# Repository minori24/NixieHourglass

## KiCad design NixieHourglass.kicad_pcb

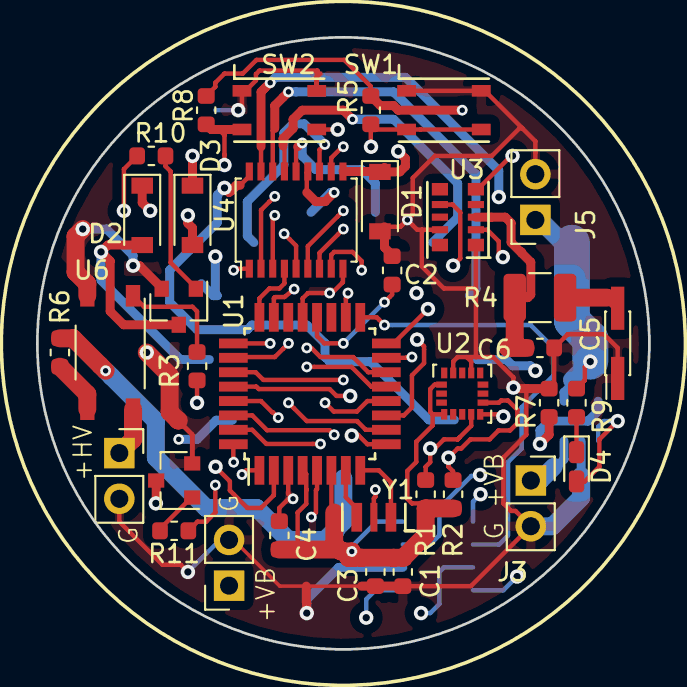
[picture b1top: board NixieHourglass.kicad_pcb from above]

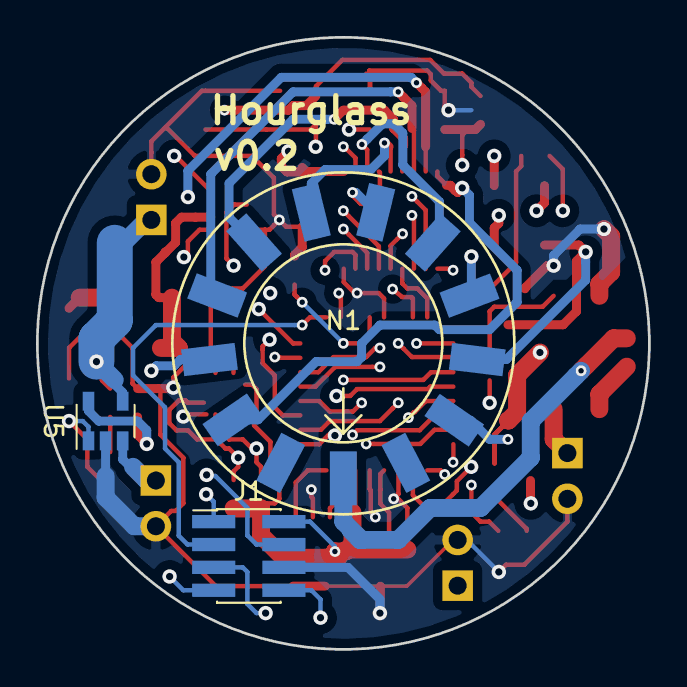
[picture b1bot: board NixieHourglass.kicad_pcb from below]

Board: 4 copper layers, 34.0 x 34.0 mm, 38 parts (3 on the bottom side), 49 nets.

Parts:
C1, C3: 1uF; C_0603_1608Metric
C2, C6: 100nF; C_0603_1608Metric
C4: 4.7uF; C_0603_1608Metric
C5: SE-5R5-D105VYV; PinHeader_2x01_P1.27mm_Vertical_SMD
D1: Zener_47V; D_SOD-123
D2, D3: GS1010FL; D_SOD-123
D4: LED; LED_0603_1608Metric_Castellated
J1: Conn_02x04_Odd_Even; PinHeader_2x04_P1.27mm_Vertical_SMD
J2: VBAT_OUT; PinSocket_1x02_P2.54mm_Vertical
J3: VBAT_IN; PinSocket_1x02_P2.54mm_Vertical
J4: HV_IN; PinSocket_1x02_P2.54mm_Vertical
J5: CHG_IN; PinSocket_1x02_P2.54mm_Vertical
N1: IN-14; IN-14_SMD
Q2, Q3: MMBTA42; SOT-23
R1, R2, R5, R8, R10, R11: 10k; R_0603_1608Metric
R3: 220; R_0603_1608Metric
R4: 1210_ROHM_MCR25JZHJ101; R_1210_3225Metric
R6: 22k; R_0603_1608Metric
R7, R9: R; R_0603_1608Metric
SW1, SW2: SKRPACE010; SW_Tactile_SKRPACE010
U1: ATmega328P-AU; TQFP-32_7x7mm_P0.8mm
U2: LIS3DHTR; LGA-16_3x3mm_P0.5mm_LayoutBorder3x5y
U3: RX8900CE
U4: TD62083AFNG; SSOP-18_4.4x6.5mm_P0.65mm
U5: MCP73832T-2ACI_OT; SOT-23-5
U6: TLP127; MFSOP6-4_4.4x3.6mm_P1.27mm
Y1: CSTCE16M0V53-R0; Xtal_Murata_CSTCE16M0V53-R0

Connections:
+5V: J5.1, R9.1, U5.4
+BATT: C1.1, C3.1, C4.1, J1.2, J2.1, J3.1, R1.1, R2.1, R5.1, R8.1, U1.4, U1.6, U1.18, U2.1, U2.14, U3.2, U5.3
+HV: J4.1, U6.6
/MISO: J1.1, U1.16
/MOSI: J1.4, U1.15
/NIX_0: R11.2, U1.12
/NIX_1: U1.13, U4.1
/NIX_2: U1.14, U4.2
/NIX_3: U1.23, U4.3
/NIX_4: U1.24, U4.4
/NIX_5: U1.25, U4.5
/NIX_6: U1.26, U4.6
/NIX_7: U1.32, U4.7
/NIX_8: U1.1, U4.8
/NIX_9: R10.2, U1.2
/NIX_ANODE: R3.2, U1.10
/RESET: J1.5, U1.29
/RXD: J1.7, U1.30
/SCK: J1.3, U1.17
/TXD: J1.8, U1.31
GND: C1.2, C2.2, C3.2, C4.2, C5.1, C6.2, D1.2, J1.6, J2.2, J3.2, J4.2, J5.2, Q2.2, Q3.2, R7.2, SW1.1, SW1.2, SW2.1, SW2.2, U1.3, U1.5, U1.21, U2.5, U2.10, U2.12, U3.1, U3.9, U4.9, U5.2, U6.3, Y1.2
unnamed: C2.1, U1.20
unnamed: C5.2, R4.1
unnamed: C6.1, R4.2, U3.3
unnamed: D1.1, D2.1, D3.1, U4.10
unnamed: D2.2, N1.9, Q2.3
unnamed: D3.2, N1.0, Q3.3
unnamed: D4.1, R9.2
unnamed: D4.2, U5.1
unnamed: N1.1, U4.18
unnamed: N1.2, U4.17
unnamed: N1.3, U4.16
unnamed: N1.4, U4.15
unnamed: N1.5, U4.14
unnamed: N1.6, U4.13
unnamed: N1.7, U4.12
unnamed: N1.8, U4.11
unnamed: N1.A, R6.2
unnamed: Q2.1, R10.1
unnamed: Q3.1, R11.1
unnamed: R3.1, U6.1
unnamed: R6.1, U6.4
unnamed: R7.1, U5.5
unnamed: U1.7, Y1.3
unnamed: U1.8, Y1.1
SCL: R1.2, U1.28, U2.4, U3.5
SDA: R2.2, U1.27, U2.6, U3.7
SW_0: R5.2, SW1.3, SW1.4, U1.9
SW_1: R8.2, SW2.3, SW2.4, U1.11

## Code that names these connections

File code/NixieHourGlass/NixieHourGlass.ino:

#define PIN_NIX_0 9
#define PIN_NIX_1 8
#define PIN_NIX_2 4
#define PIN_NIX_4 2
#define PIN_NIX_3 3
#define PIN_NIX_5 A3
#define PIN_NIX_6 A2
#define PIN_NIX_7 A1
#define PIN_NIX_8 A0
#define PIN_NIX_9 10
#define PIN_SW_0 5
#define PIN_SW_1 7
#define PIN_NIX_ANODE 6

void setup() {
  // put your setup code here, to run once:
  Serial.begin(115200);
  pinMode(PIN_NIX_0, OUTPUT);
  pinMode(PIN_NIX_1, OUTPUT);
  pinMode(PIN_NIX_2, OUTPUT);
  pinMode(PIN_NIX_3, OUTPUT);
  pinMode(PIN_NIX_4, OUTPUT);
  pinMode(PIN_NIX_5, OUTPUT);
  pinMode(PIN_NIX_6, OUTPUT);
  pinMode(PIN_NIX_7, OUTPUT);
  pinMode(PIN_NIX_8, OUTPUT);
  pinMode(PIN_NIX_9, OUTPUT);
  pinMode(PIN_NIX_ANODE, OUTPUT);
  digitalWrite(PIN_NIX_ANODE, HIGH);
}                                                                                                                                                         

void loop() {
  // put your main code here, to run repeatedly:
  while(1)
  { 
    digitalWrite(PIN_NIX_0, HIGH);
    digitalWrite(PIN_NIX_9, LOW);
    delay(1000);
    digitalWrite(PIN_NIX_1, HIGH);
    digitalWrite(PIN_NIX_0, LOW);
    delay(2000);
    digitalWrite(PIN_NIX_2, HIGH);
    digitalWrite(PIN_NIX_1, LOW);
    delay(2000);
    digitalWrite(PIN_NIX_3, HIGH);
    digitalWrite(PIN_NIX_2, LOW);
    delay(2000);
    digitalWrite(PIN_NIX_4, HIGH);
    digitalWrite(PIN_NIX_3, LOW);
    delay(2000);
    digitalWrite(PIN_NIX_5, HIGH);
    digitalWrite(PIN_NIX_4, LOW);
    delay(2000);
    digitalWrite(PIN_NIX_6, HIGH);
    digitalWrite(PIN_NIX_5, LOW);
    delay(2000);
    digitalWrite(PIN_NIX_7, HIGH);
    digitalWrite(PIN_NIX_6, LOW);
    delay(2000);
    digitalWrite(PIN_NIX_8, HIGH);
    digitalWrite(PIN_NIX_7, LOW);
    delay(2000);
    digitalWrite(PIN_NIX_9, HIGH);
    digitalWrite(PIN_NIX_8, LOW);
    delay(2000);
 } 
}

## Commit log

2019-02-01 routing
2019-04-28 add zener
2019-04-28 Add optocoupler
